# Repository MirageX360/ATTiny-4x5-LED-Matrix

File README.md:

# ATTiny 4x5 LED Matrix PCB Project
A 4x5 LED Matrix that can light up in pre-programmed sequences or display simple symbols or images.

This Project was created for Hack Club 8-Pin Grant!

Link: https://8-pin-grant.hackclub.com/

Checklist:

- [x] Settle on an idea
- [x] Research on designs and functions
- [x] Create a rough drawing/sketch/outline
- [x] Create Wiring Diagram/Schematic
- [x] Create PCB layout
- [x] Sanity check-in with Slack
- [X] Finalize BOM
- [x] Finalize PCB
- [x] Submit to 8-Pin Grant
- [ ] Assemble Project
- [ ] Program Project
- [ ] Take a video of it in action and submit it to the SlackLink

BOM:

| Component | Digikey Part Number | Quantity |
| :--- | :--- | :---: |
| ATTiny85 | ATTINY85-20PU-ND | 1 |
| 8-pin DIP IC Socket | 1175-1486-ND | 1 |
| 5mm LED | 160-LTL2R3KYD-EM-ND | 20 |
| 100Ω Resistor | 100XBK-ND | 5 |
| Coin Battery Holder | BS-7-ND | 1 |
| Slide-Switch | EG1903-ND | 1 |

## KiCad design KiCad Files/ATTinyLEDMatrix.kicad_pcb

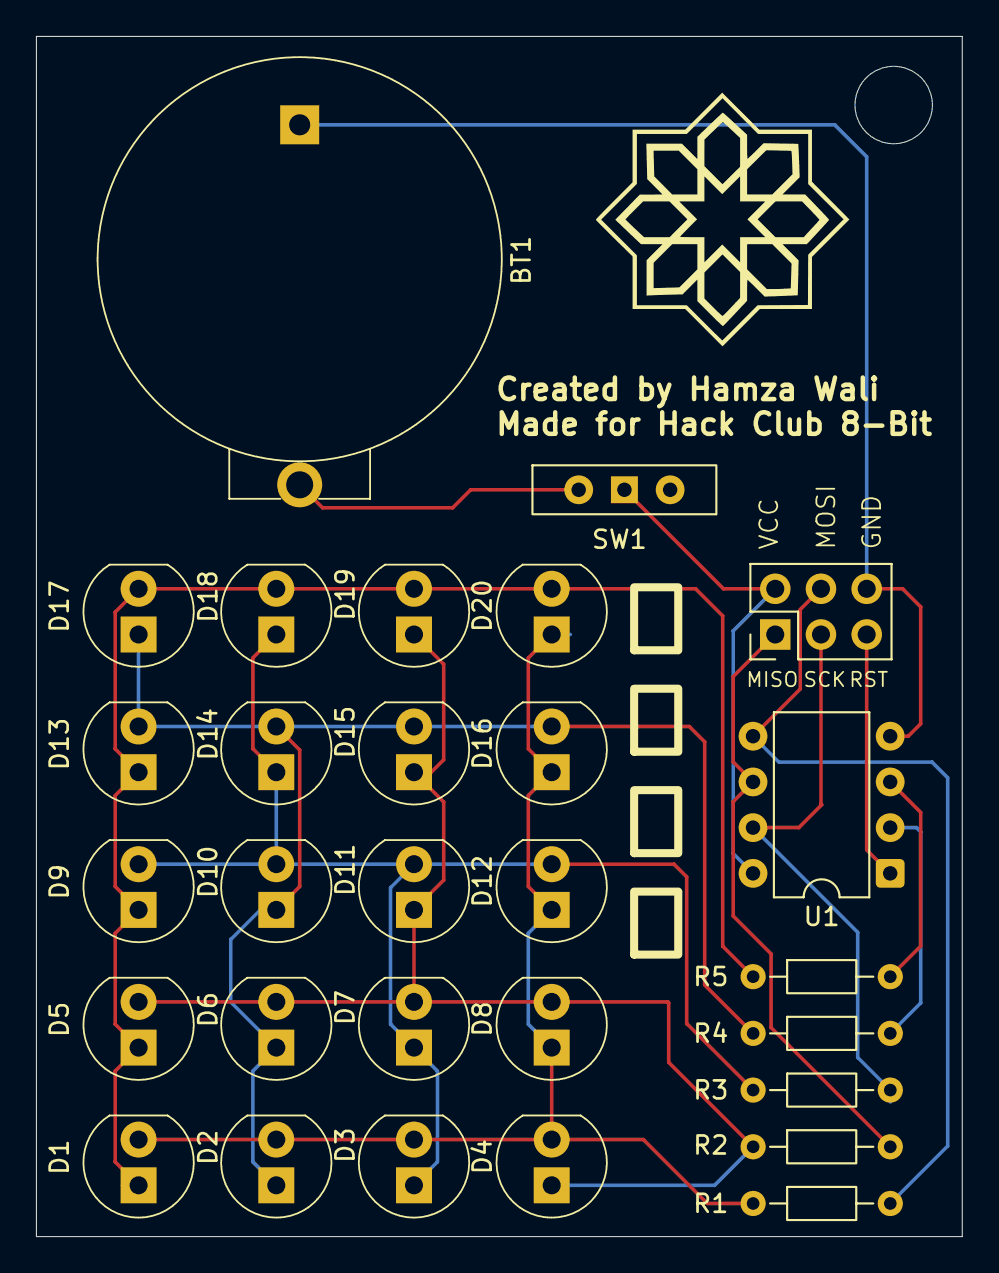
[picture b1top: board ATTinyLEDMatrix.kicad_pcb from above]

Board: 2 copper layers, 51.4 x 66.7 mm, 29 parts (0 on the bottom side), 14 nets.

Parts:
BT1: Battery_Cell; Battery_Holder_Coin_2032_BS-7
D1, D2, D3, D4, D5, D6, D7, D8, D9, D10, D11, D12, D13, D14, D15, D16, D17, D18, D19, D20: LED; LED_5mm_Radial
JP1: 6pinconnector; PinHeader_2x03_P2.54mm_Vertical
R1, R2, R3, R4, R5: R; R_Axial_DIN0204_L3.6mm_D1.6mm_P7.62mm_Horizontal
SW1: SW_Wuerth_450301014042; SW_Slide-03_Wuerth-WS-SLTV_10x2.5x6.4_P2.54mm
U1: ATtiny85-20P; DIP-8_W7.62mm

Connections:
GND: BT1.1 (+_1), JP1.6 (GND), U1.4 (GND)
unnamed: BT1.B+ (-_2), SW1.B+ (C_2)
unnamed: D1.2 (A), D2.2 (A), D3.2 (A), D4.2 (A), D8.1 (K), D12.1 (K), D16.1 (K), D20.1 (K), R1.1
unnamed: D1.1 (K), D5.1 (K), D9.1 (K), D13.1 (K), D17.2 (A), D18.2 (A), D19.2 (A), D20.2 (A), R5.1
unnamed: D3.1 (K), D7.1 (K), D9.2 (A), D10.2 (A), D11.2 (A), D12.2 (A), D14.1 (K), D18.1 (K), R3.1
unnamed: D2.1 (K), D6.1 (K), D10.1 (K), D13.2 (A), D14.2 (A), D15.2 (A), D16.2 (A), D17.1 (K), R4.1
unnamed: D4.1 (K), D5.2 (A), D6.2 (A), D7.2 (A), D8.2 (A), D11.1 (K), D15.1 (K), D19.1 (K), R2.1
PB0: JP1.4 (MOSI), R1.2, U1.5 (AREF/PB0)
PB1: JP1.1 (MISO), R2.2, U1.6 (PB1)
PB2: JP1.3 (SCK), R3.2, U1.7 (PB2)
PB3: R4.2, U1.2 (XTAL1/PB3)
PB4: R5.2, U1.3 (XTAL2/PB4)
PB5: JP1.5 (RST), U1.1 (~RESET/PB5)
VCC: JP1.2 (VCC), SW1.2 (B_1), U1.8 (VCC)
